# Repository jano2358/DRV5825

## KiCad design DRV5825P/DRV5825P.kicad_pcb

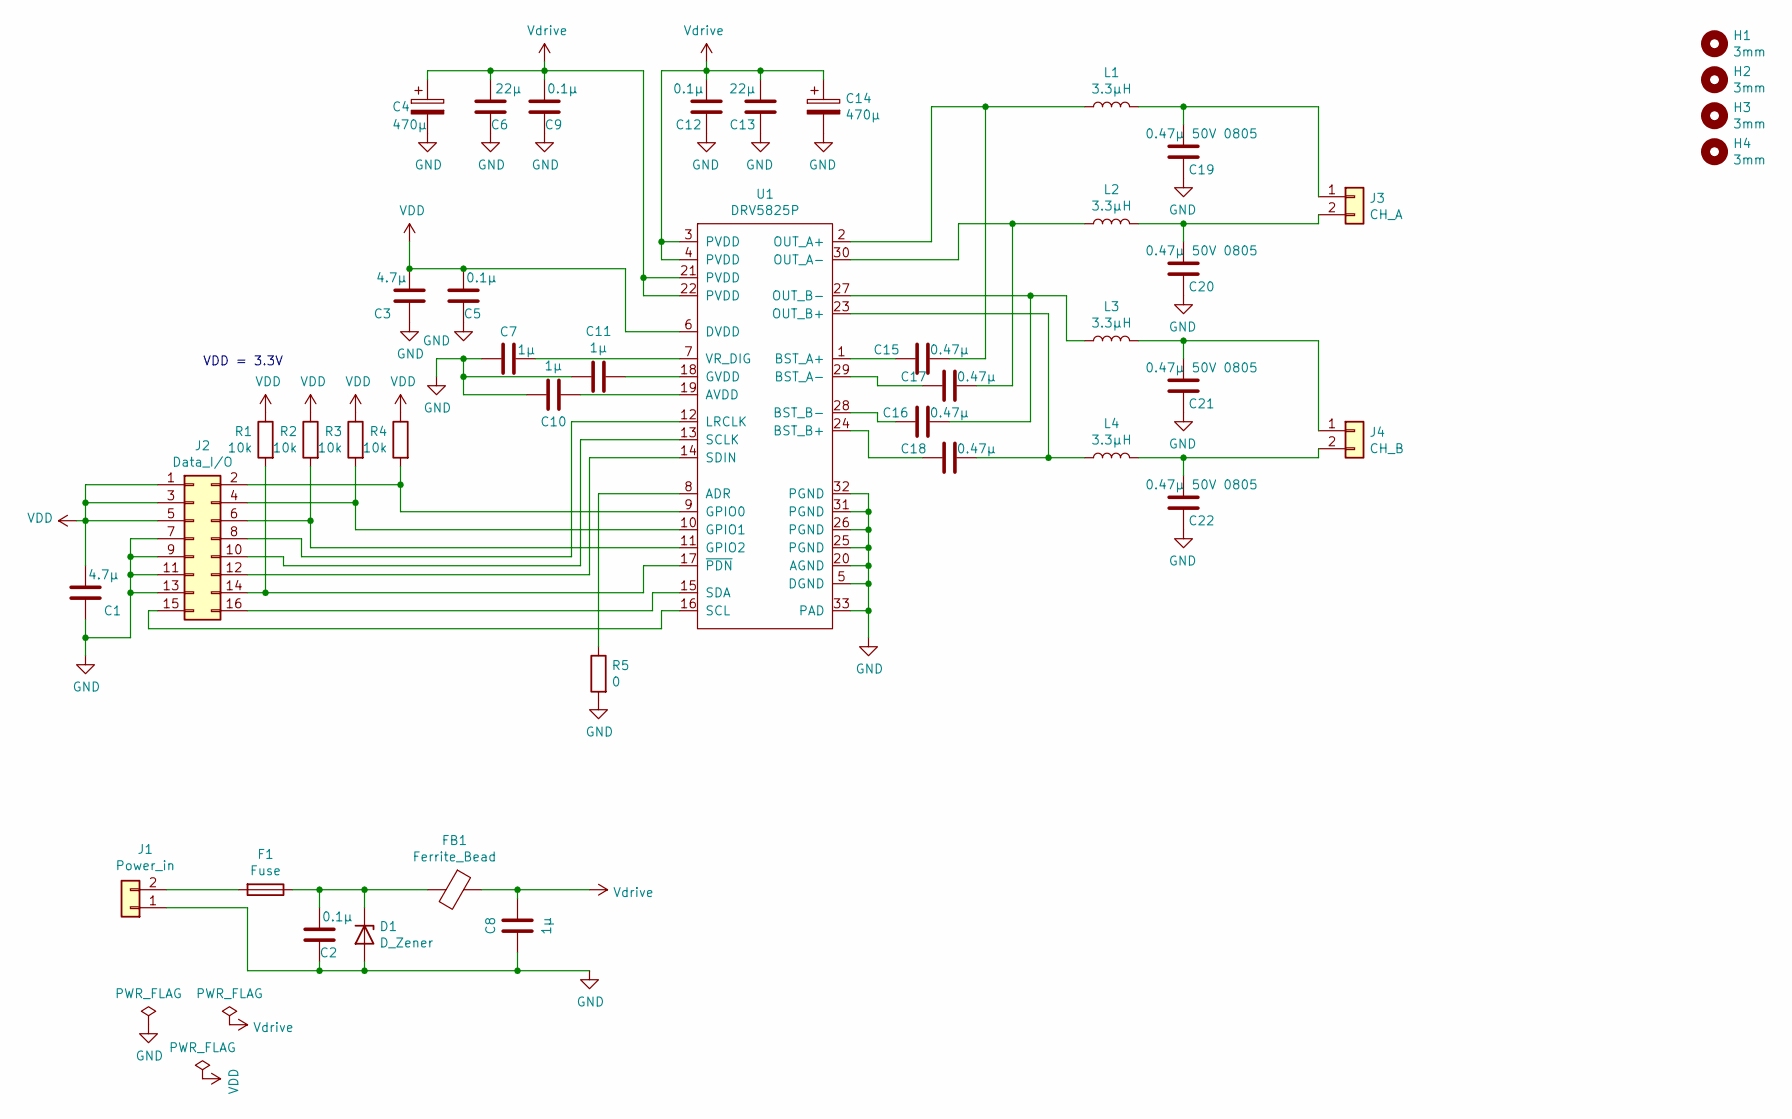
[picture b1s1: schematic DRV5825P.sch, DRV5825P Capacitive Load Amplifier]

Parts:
C1, C3: 4.7µ; C_0805_2012Metric
C2, C5, C9, C12: 0.1µ; C_0603_1608Metric
C4, C14: 470µ; CP_Elec_10x14.3
C6, C13: 22µ; C_1206_3216Metric
C7, C8, C10, C11: 1µ; C_0603_1608Metric
C15, C16, C17, C18: 0.47µ; C_0603_1608Metric
C19, C20, C21, C22: 0.47µ 50V 0805; C_0805_2012Metric
D1: D_Zener; D_SMB
F1: Fuse; Fuse_1206_3216Metric
FB1: Ferrite_Bead; L_0805_2012Metric
H1, H2, H3, H4: 3mm; MountingHole_3.2mm_M3_Pad
J1: Power_in; PhoenixContact_MCV_1,5_2-G-3.5_1x02_P3.50mm_Vertical
J2: Data_I/O; IDC-Header_2x08_P2.54mm_Vertical
J3: CH_A; PhoenixContact_MCV_1,5_2-G-3.5_1x02_P3.50mm_Vertical
J4: CH_B; PhoenixContact_MCV_1,5_2-G-3.5_1x02_P3.50mm_Vertical
L1, L2, L3, L4: 3.3µH; L_Sumida_CDMC6D28_7.25x6.5mm; PartNumber 0630CDMCCDS-3R3MC
R1, R2, R3, R4: 10k; R_0603_1608Metric
R5: 0; R_0603_1608Metric
U1: DRV5825P; QFN-32-1EP_5x5mm_P0.5mm_EP3.3x3.3mm

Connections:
GND: C1.2, C2.2, C3.2, C4.2, C5.2, C6.2, C7.2, C8.1, C9.2, C10.2, C11.2, C12.2, C13.2, C14.2, C19.2, C20.2, C21.2, C22.2, D1.2 (A), J1.1, J2.7, J2.9, J2.11, J2.13, R5.2, U1.5 (DGND), U1.20 (AGND), U1.25 (PGND), U1.26 (PGND), U1.31 (PGND), U1.32 (PGND), U1.33 (PAD); also elsewhere on the board
unnamed: C2.1, D1.1 (K), F1.1, FB1.2
unnamed: C7.1, U1.7 (VR_DIG)
unnamed: C10.1, U1.19 (AVDD)
unnamed: C11.1, U1.18 (GVDD)
unnamed: C15.1, L1.1, U1.2 (OUT_A+)
unnamed: C15.2, U1.1 (BST_A+)
unnamed: C16.1, L3.1, U1.27 (OUT_B-)
unnamed: C16.2, U1.28 (BST_B-)
unnamed: C17.1, L2.1, U1.30 (OUT_A-)
unnamed: C17.2, U1.29 (BST_A-)
unnamed: C18.1, L4.1, U1.23 (OUT_B+)
unnamed: C18.2, U1.24 (BST_B+)
unnamed 13: C19.1, J3.1, L1.2; also elsewhere on the board
unnamed 14: C20.1, J3.2, L2.2; also elsewhere on the board
unnamed 15: C21.1, J4.1, L3.2; also elsewhere on the board
unnamed 16: C22.1, J4.2, L4.2; also elsewhere on the board
unnamed 17: F1.2, J1.2; also elsewhere on the board
unnamed 18: J2.2, R4.2, U1.9 (GPIO0); also elsewhere on the board
unnamed 19: J2.4, R3.2, U1.10 (GPIO1); also elsewhere on the board
unnamed 20: J2.6, R2.2, U1.11 (GPIO2); also elsewhere on the board
unnamed 21: J2.8, U1.12 (LRCLK); also elsewhere on the board
unnamed 22: J2.10, U1.13 (SCLK); also elsewhere on the board
unnamed 23: J2.12, U1.14 (SDIN); also elsewhere on the board
unnamed 24: J2.14, R1.2, U1.17 (~PDN); also elsewhere on the board
unnamed 25: J2.15, U1.16 (SCL); also elsewhere on the board
unnamed 26: J2.16, U1.15 (SDA); also elsewhere on the board
unnamed: R5.1, U1.8 (ADR)
VDD: C1.1, C3.1, C5.1, J2.1, J2.3, J2.5, R1.1, R2.1, R3.1, R4.1, U1.6 (DVDD); also elsewhere on the board
Vdrive: C4.1, C6.1, C8.2, C9.1, C12.1, C13.1, C14.1, FB1.1, U1.3 (PVDD), U1.4 (PVDD), U1.21 (PVDD), U1.22 (PVDD)

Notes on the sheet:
VDD = 3.3V

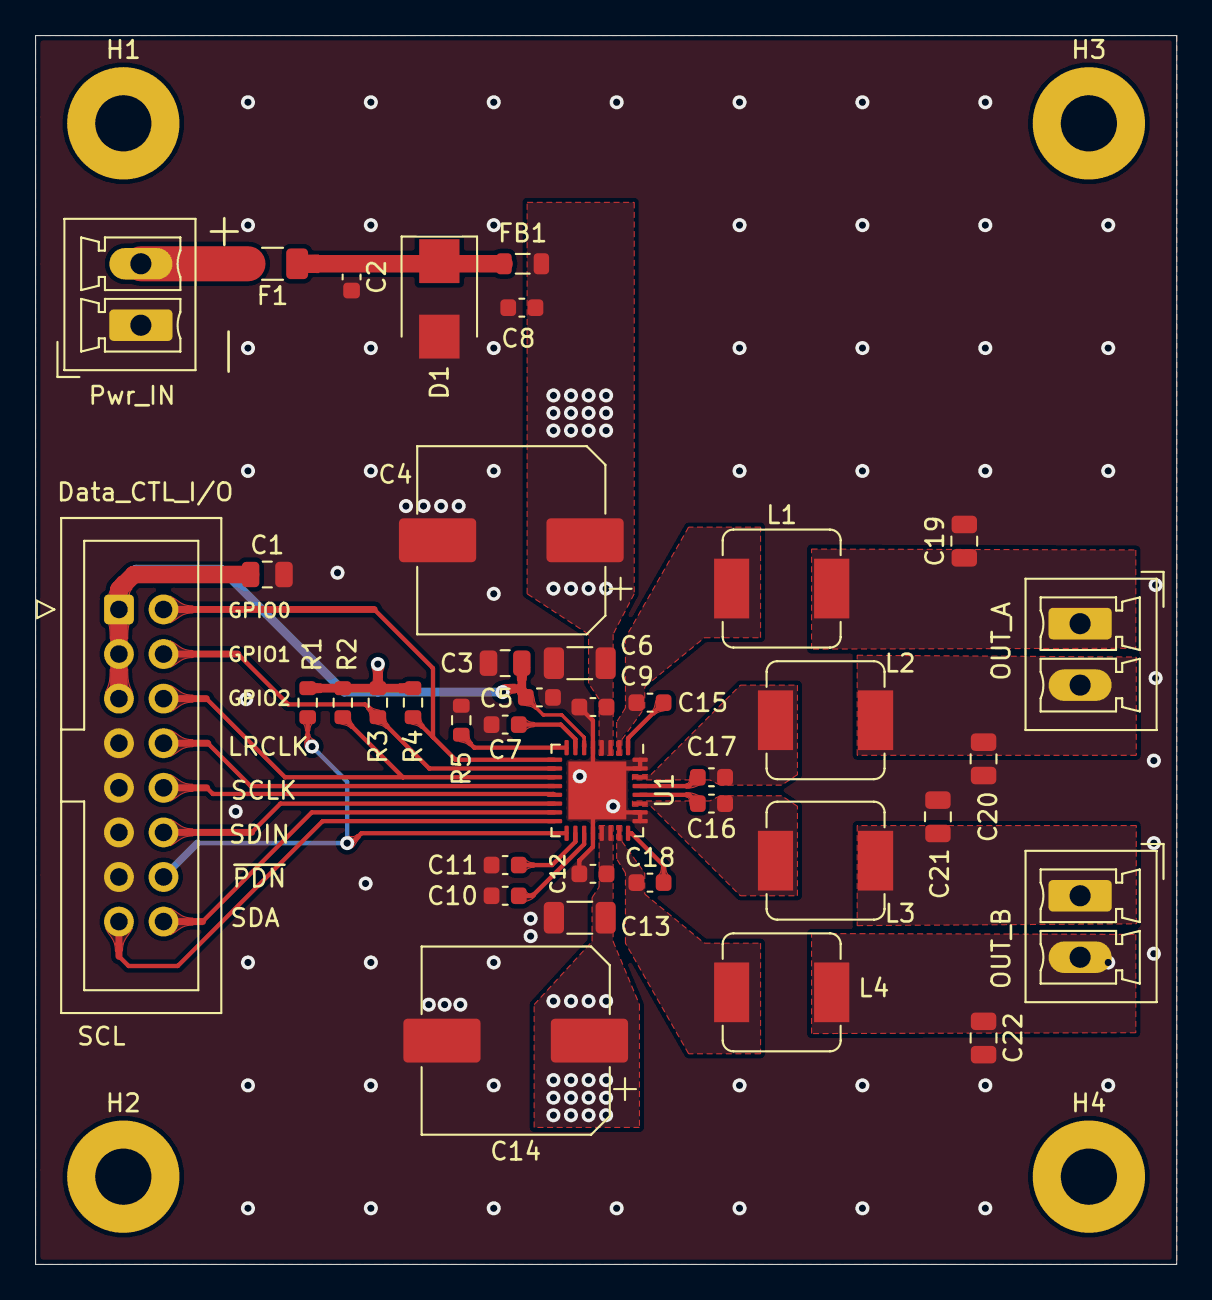
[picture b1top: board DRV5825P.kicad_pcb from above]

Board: 2 copper layers, 65.0 x 70.0 mm, 43 parts (0 on the bottom side), 30 nets.

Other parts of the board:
Data_CTL_I/O: Data_I/O; IDC-Header_2x08_P2.54mm_Vertical
OUT_A: CH_A; PhoenixContact_MCV_1,5_2-G-3.5_1x02_P3.50mm_Vertical
OUT_B: CH_B; PhoenixContact_MCV_1,5_2-G-3.5_1x02_P3.50mm_Vertical
Pwr_IN: Power_in; PhoenixContact_MCV_1,5_2-G-3.5_1x02_P3.50mm_Vertical

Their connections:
GND: Data_CTL_I/O.7, Data_CTL_I/O.9, Data_CTL_I/O.11, Data_CTL_I/O.13, Pwr_IN.1; also elsewhere on the board
unnamed 13: OUT_A.1; also elsewhere on the board
unnamed 14: OUT_A.2; also elsewhere on the board
unnamed 15: OUT_B.1; also elsewhere on the board
unnamed 16: OUT_B.2; also elsewhere on the board
unnamed 17: Pwr_IN.2; also elsewhere on the board
unnamed 18: Data_CTL_I/O.2; also elsewhere on the board
unnamed 19: Data_CTL_I/O.4; also elsewhere on the board
unnamed 20: Data_CTL_I/O.6; also elsewhere on the board
unnamed 21: Data_CTL_I/O.8; also elsewhere on the board
unnamed 22: Data_CTL_I/O.10; also elsewhere on the board
unnamed 23: Data_CTL_I/O.12; also elsewhere on the board
unnamed 24: Data_CTL_I/O.14; also elsewhere on the board
unnamed 25: Data_CTL_I/O.15; also elsewhere on the board
unnamed 26: Data_CTL_I/O.16; also elsewhere on the board
VDD: Data_CTL_I/O.1, Data_CTL_I/O.3, Data_CTL_I/O.5; also elsewhere on the board

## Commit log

2021-05-24 datasheet aded
2021-05-24 drv lib as local
2021-06-06 pcb design
2021-06-06 teardrops added
2021-06-14 agadöjlk
2021-07-04 gerbers ready
